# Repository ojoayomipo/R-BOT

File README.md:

# R-BOT
R-BOT is a PCB designed for a robot which can be controlled using bluetooth, IR. It also has slots for the HC-SR04 ultrasonic sensor from which an autonomous vehicle may be constructed.
This repository contains the KICAD design files for R-BOT

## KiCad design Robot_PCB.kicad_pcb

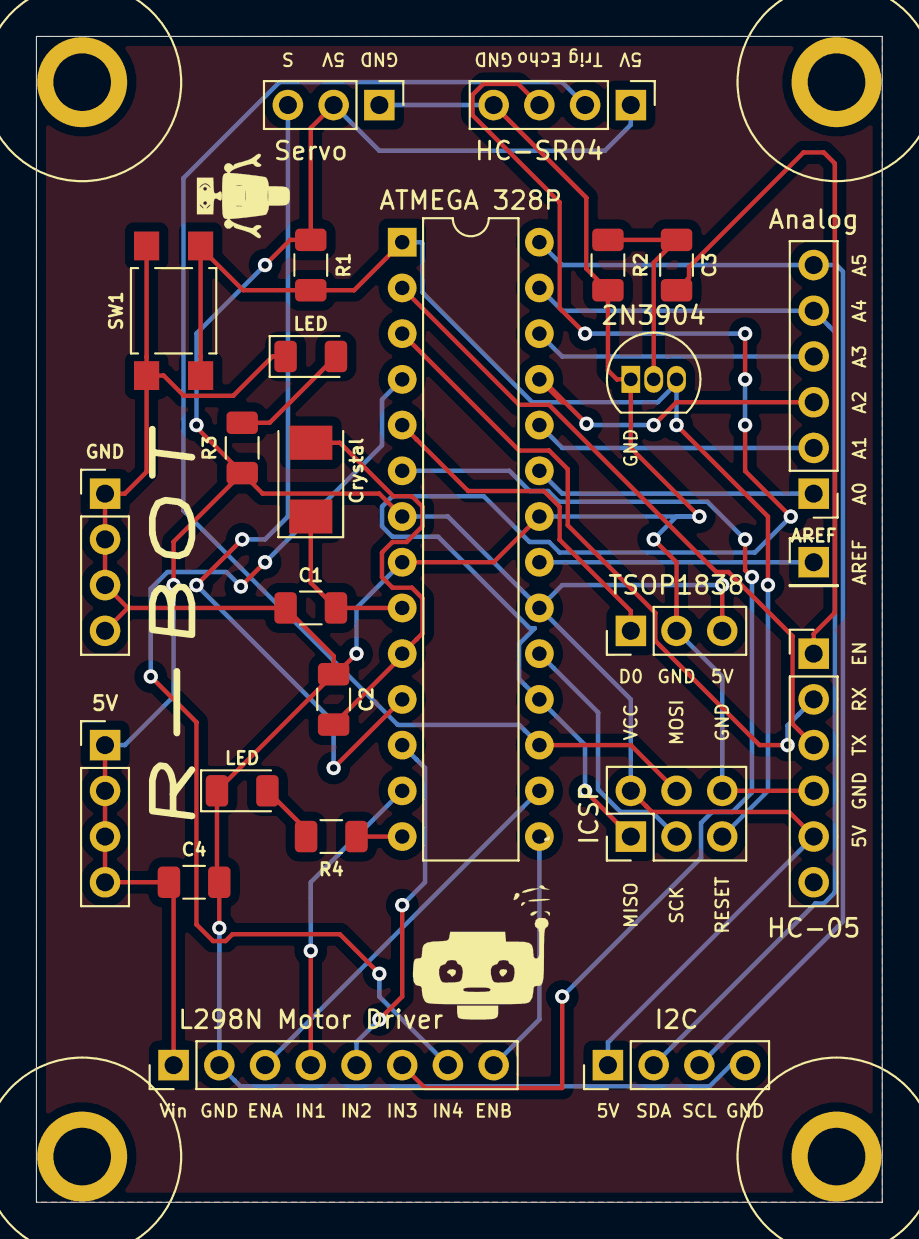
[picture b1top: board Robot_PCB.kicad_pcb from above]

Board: 2 copper layers, 47.0 x 64.8 mm, 25 parts (0 on the bottom side), 30 nets.

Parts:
2N3904: 2N3904; TO-92_Inline
5V: +5V RAIL; PinHeader_1x04_P2.54mm_Vertical
AREF: A0-A; PinHeader_1x06_P2.54mm_Vertical
ATMEGA 328P: ATmega328-PU; DIP-28_W7.62mm
Analog: AREF; PinHeader_1x01_P2.54mm_Vertical
C1, C2: 22pF; C_1206_3216Metric
C3: 10nF; C_1206_3216Metric
C4: 10uF; C_1206_3216Metric
Crystal: Crystal; Crystal_SMD_Abracon_ABM3-2Pin_5.0x3.2mm
GND: GND; PinHeader_1x04_P2.54mm_Vertical
HC-05: HC-05; PinHeader_1x06_P2.54mm_Vertical
HC-SR04: Conn_01x04; PinHeader_1x04_P2.54mm_Vertical
I2C: SPI; PinHeader_1x04_P2.54mm_Vertical
ICSP: AVR-ISP-6; PinHeader_2x03_P2.54mm_Vertical
L298N Motor Driver: L298; PinHeader_1x08_P2.54mm_Vertical
LED: LED; LED_1206_3216Metric
LED#2: LED; LED_1206_3216Metric
R1, R2: 10k; R_1206_3216Metric
R3, R4: 220; R_1206_3216Metric
SW1: SW_Push; SW_SPST_TL3305A
Servo: Conn_01x03; PinHeader_1x03_P2.54mm_Vertical
TSOP1838: TSOP; PinHeader_1x03_P2.54mm_Vertical

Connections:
+5V: 5V.1, 5V.2, 5V.3, 5V.4, ATMEGA 328P.7, ATMEGA 328P.20, C4.1, HC-05.5, HC-SR04.1, I2C.1, ICSP.2, L298N Motor Driver.1, R1.1, R3.1, Servo.2, TSOP1838.3
DO: ATMEGA 328P.5, TSOP1838.1
ECHO: ATMEGA 328P.18, HC-SR04.3, ICSP.1
ENA: ATMEGA 328P.16, L298N Motor Driver.3
ENB: ATMEGA 328P.15, L298N Motor Driver.8
GND: 2N3904.1, ATMEGA 328P.8, ATMEGA 328P.22, C1.1, C2.1, C4.2, GND.1, GND.2, GND.3, GND.4, HC-05.4, HC-SR04.4, I2C.4, ICSP.6, L298N Motor Driver.2, LED.1, LED#2.1, R2.2, SW1.1, Servo.1, TSOP1838.2
IN1: ATMEGA 328P.13, L298N Motor Driver.4
IN2: ATMEGA 328P.12, L298N Motor Driver.5
IN3: ATMEGA 328P.6, L298N Motor Driver.6
IN4: ATMEGA 328P.4, L298N Motor Driver.7
LED: ATMEGA 328P.14, R4.1
unnamed: 2N3904.2, C3.1, R2.1
unnamed: LED#2.2, R3.2
unnamed: LED.2, R4.2
unnamed: AREF.1, ATMEGA 328P.23
unnamed: AREF.2, ATMEGA 328P.24
unnamed: AREF.3, ATMEGA 328P.25
unnamed: AREF.4, ATMEGA 328P.26
unnamed: ATMEGA 328P.21, Analog.1
RESET: 2N3904.3, ATMEGA 328P.1, ICSP.5, R1.2, SW1.2
RX: ATMEGA 328P.2, HC-05.3
S: ATMEGA 328P.11, Servo.3
SCK: ATMEGA 328P.19, ICSP.3
SCL: AREF.6, ATMEGA 328P.28, I2C.3
SDA: AREF.5, ATMEGA 328P.27, I2C.2
STATE: C3.2, HC-05.1
TRIG: ATMEGA 328P.17, HC-SR04.2, ICSP.4
TX: ATMEGA 328P.3, HC-05.2
XTAL1: ATMEGA 328P.9, C1.2, Crystal.1
XTAL2: ATMEGA 328P.10, C2.2, Crystal.2
